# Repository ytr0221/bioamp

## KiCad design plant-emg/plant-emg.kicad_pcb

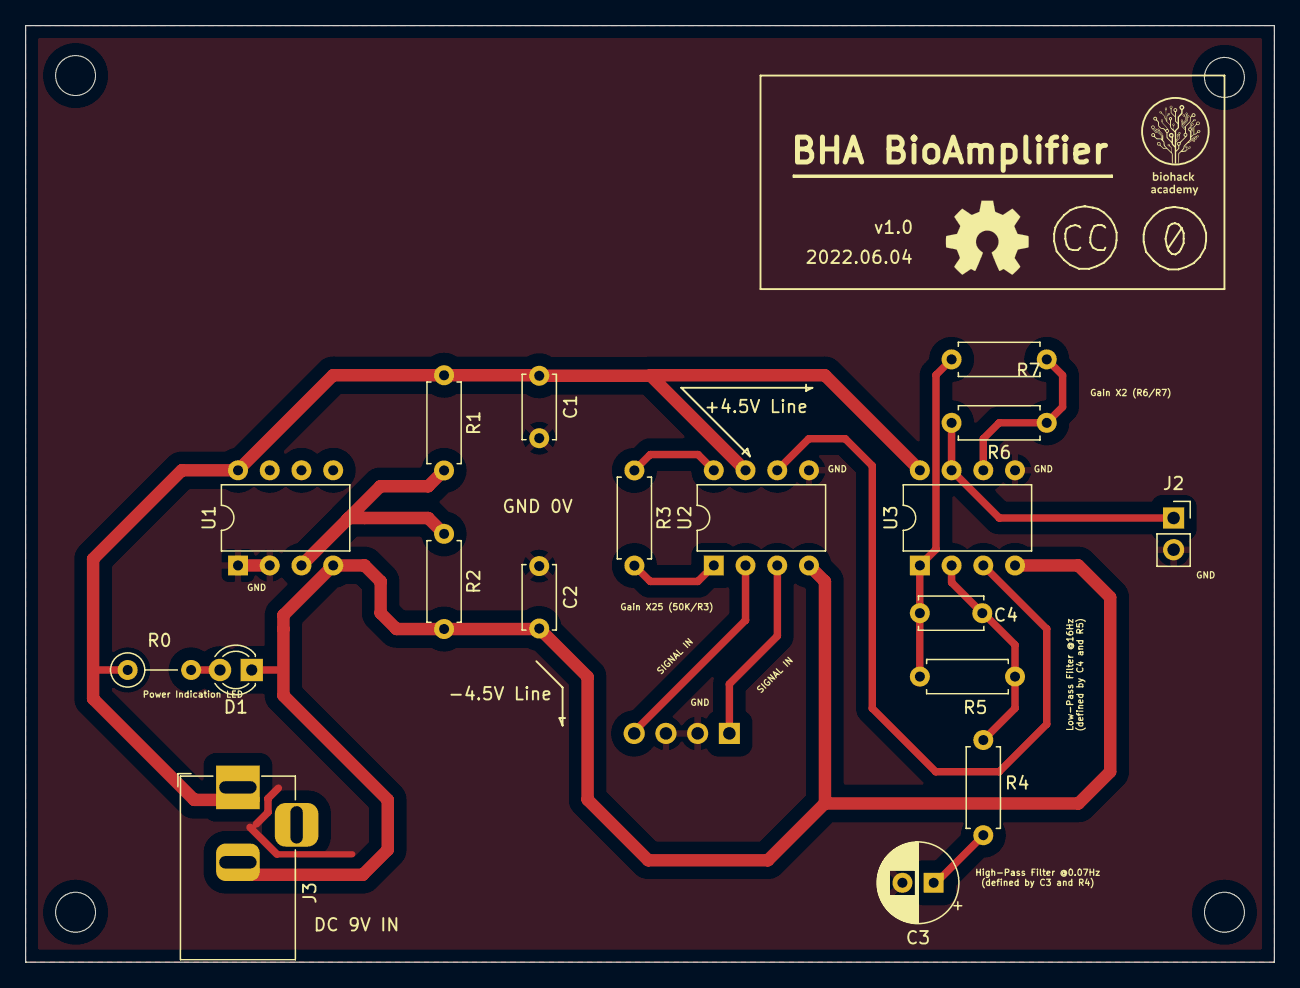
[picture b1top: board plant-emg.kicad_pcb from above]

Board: 2 copper layers, 100.0 x 75.0 mm, 23 parts (1 on the bottom side), 14 nets.

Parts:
C1, C2: 10u; C_Disc_D5.0mm_W2.5mm_P5.00mm
C3: 220u; CP_Radial_D6.3mm_P2.50mm
C4: 0.1u; C_Disc_D5.0mm_W2.5mm_P5.00mm
D1: LED_3V_20mA; LED_D3.0mm
J1: Conn_01x04_Female; PinSocket_1x04_P2.54mm_Horizontal
J2: Conn_01x02_Female; PinSocket_1x02_P2.54mm_Vertical
J3: Barrel_Jack; BarrelJack_Horizontal
MH1, MH3, MH4: MountingHole_3.2mm_M3
MT2: MountingHole_3.2mm_M3
R0: 300; R_Axial_DIN0207_L6.3mm_D2.5mm_P5.08mm_Vertical
R1, R2: 2.2k; R_Axial_DIN0207_L6.3mm_D2.5mm_P7.62mm_Horizontal
R3: 2k; R_Axial_DIN0207_L6.3mm_D2.5mm_P7.62mm_Horizontal
R4, R7: 10k; R_Axial_DIN0207_L6.3mm_D2.5mm_P7.62mm_Horizontal
R5: 100k; R_Axial_DIN0207_L6.3mm_D2.5mm_P7.62mm_Horizontal
R6: 20k; R_Axial_DIN0207_L6.3mm_D2.5mm_P7.62mm_Horizontal
U1, U3: TLC2272-Q1_D_8; DIP-8_W7.62mm
U2: LT1167CN8; DIP-8_W7.62mm

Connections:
0V: C1.2, C2.1, C3.2, J1.2, J1.3, J2.2, U1.1 (1OUT), U1.2 (1IN-), U2.5 (REF), U3.5 (2IN+)
4.5V: C1.1, J3.1, R0.1, R1.1, U1.8 (VDD+), U2.7 (+VS), U3.8 (VDD+)
-4.5V: C2.2, D1.1 (K), J3.2, R1.2, R2.1, R2.2, U1.4 (VDD-/GND), U2.4 (-VS), U3.4 (VDD-/GND)
unnamed: C3.1, R4.2
unnamed: C4.1, R5.1, R7.2, U3.1 (1OUT)
unnamed: C4.2, R4.1, R5.2, U3.2 (1IN-)
unnamed: J2.1, R6.2, U3.7 (2OUT)
unnamed: D1.2 (A), R0.2
unnamed: R3.1, U2.8 (RG)
unnamed: R3.2, U2.1 (RG_2)
unnamed: R6.1, R7.1, U3.6 (2IN-)
unnamed: J1.4, U2.2 (-IN)
unnamed: J1.1, U2.3 (+IN)
unnamed: U2.6 (OUTPUT), U3.3 (1IN+)

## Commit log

2022-06-03 first
2022-06-03 added board
2022-06-03 rename
2022-07-11 remane
